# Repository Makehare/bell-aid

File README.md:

# bell-aid

Bell Aid

Release v1.3.1.

## Contents

- `docs/`
- `electronics/`
- `firmware/`
- `mechanics/`

## License

Hardware CERN-OHL-P-2.0, firmware MIT, documentation and renders CC-BY-4.0 (see LICENSE).

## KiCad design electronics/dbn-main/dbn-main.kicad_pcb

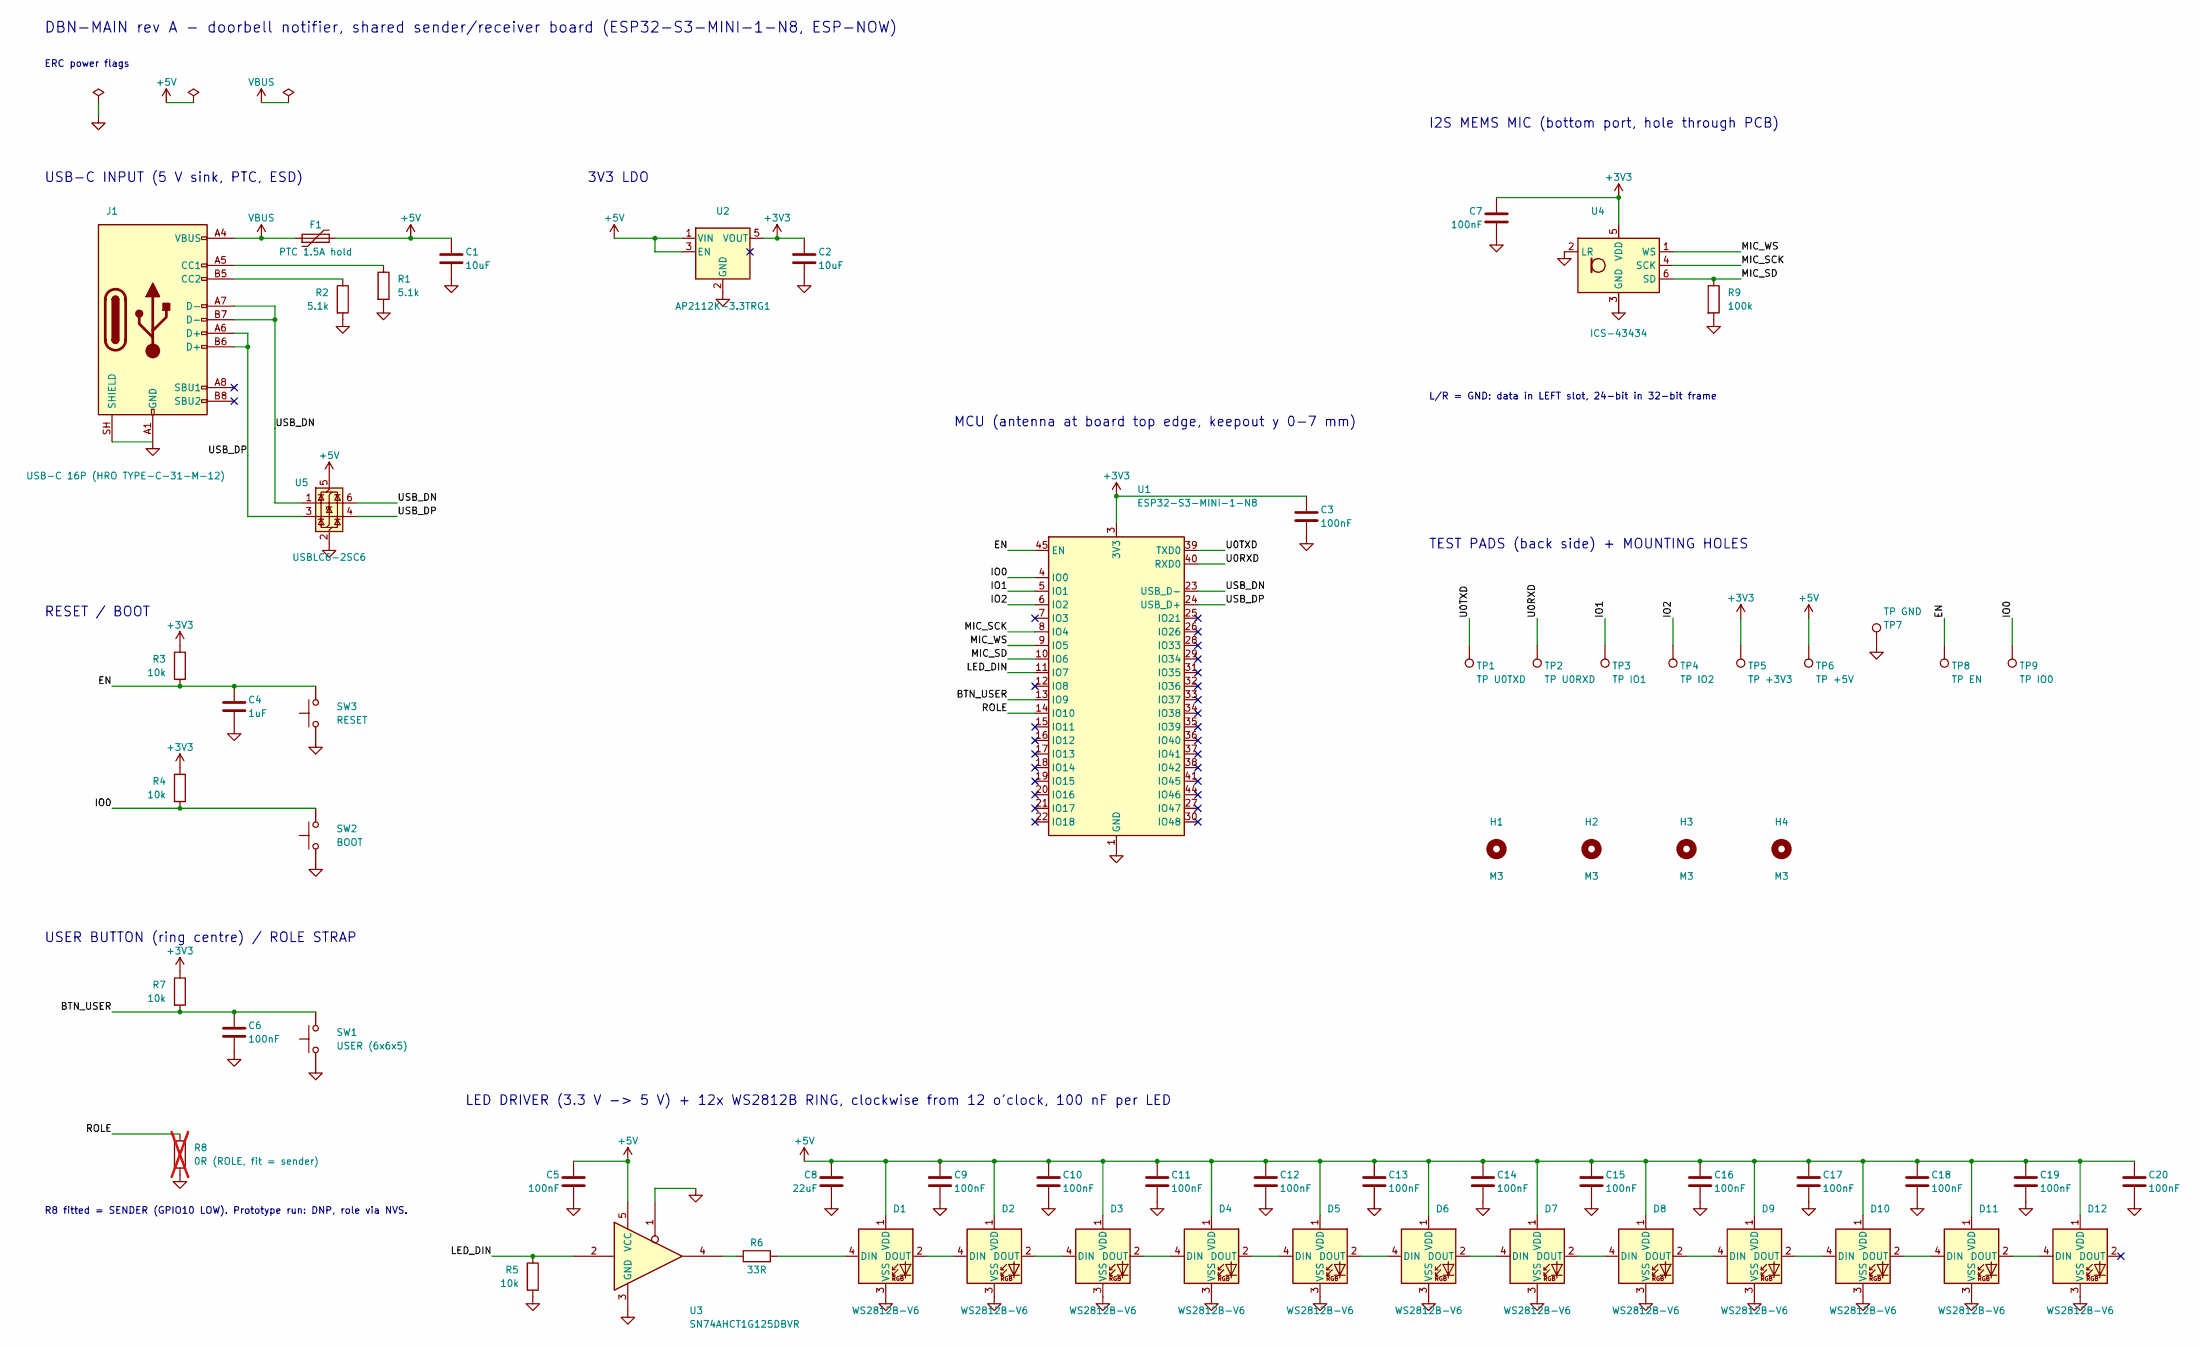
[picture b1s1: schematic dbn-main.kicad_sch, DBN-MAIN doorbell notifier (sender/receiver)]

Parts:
C1, C2: 10uF; C_0805_2012Metric; MPN CL21A106KAYNNNE; LCSC C15850
C3, C5, C6, C7, C9, C10, C11, C12, C13, C14, C15, C16, C17, C18, C19, C20: 100nF; C_0603_1608Metric; MPN CC0603KRX7R9BB104; LCSC C14663
C4: 1uF; C_0603_1608Metric; MPN CL10A105KB8NNNC; LCSC C15849
C8: 22uF; C_0805_2012Metric; MPN CL21A226MAQNNNE; LCSC C45783
D1, D2, D3, D4, D5, D6, D7, D8, D9, D10, D11, D12: WS2812B-V6; LED_WS2812B_PLCC4_5.0x5.0mm_P3.2mm; MPN WS2812B-V6; LCSC C52917433
F1: PTC 1.5A hold; Fuse_1206_3216Metric; MPN 1206L150THWR; LCSC C118413
H1, H2, H3, H4: M3; MountingHole_3.2mm_M3_NPTH
J1: USB-C 16P (HRO TYPE-C-31-M-12); USB_C_Receptacle_HRO_TYPE-C-31-M-12; MPN TYPE-C-31-M-12; LCSC C165948
R1, R2: 5.1k; R_0603_1608Metric; MPN 0603WAF5101T5E; LCSC C23186
R3, R4, R5, R7: 10k; R_0603_1608Metric; MPN 0603WAF1002T5E; LCSC C25804
R6: 33R; R_0603_1608Metric; MPN 0603WAF330JT5E; LCSC C23140
R8: 0R (ROLE, fit = sender); R_0603_1608Metric; MPN 0603WAF0000T5E; LCSC C21189; not fitted
R9: 100k; R_0603_1608Metric; MPN 0603WAF1003T5E; LCSC C25803
SW1: USER (6x6x5); SW_K2-1102SP-C4SC-04_6x6x5mm; MPN K2-1102SP-C4SC-04; LCSC C127509
SW2: BOOT; SW_Push_1P1T_XKB_TS-1187A; MPN TS-1187A-B-A-B; LCSC C318884
SW3: RESET; SW_Push_1P1T_XKB_TS-1187A; MPN TS-1187A-B-A-B; LCSC C318884
TP1: TP U0TXD; TestPoint_Pad_D1.5mm
TP2: TP U0RXD; TestPoint_Pad_D1.5mm
TP3: TP IO1; TestPoint_Pad_D1.5mm
TP4: TP IO2; TestPoint_Pad_D1.5mm
TP5: TP +3V3; TestPoint_Pad_D1.5mm
TP6: TP +5V; TestPoint_Pad_D1.5mm
TP7: TP GND; TestPoint_Pad_D1.5mm
TP8: TP EN; TestPoint_Pad_D1.5mm
TP9: TP IO0; TestPoint_Pad_D1.5mm
U1: ESP32-S3-MINI-1-N8; ESP32-S3-MINI-1; MPN ESP32-S3-MINI-1-N8; LCSC C2913206
U2: AP2112K-3.3TRG1; SOT-23-5; MPN AP2112K-3.3TRG1; LCSC C51118
U3: SN74AHCT1G125DBVR; SOT-23-5; MPN SN74AHCT1G125DBVR; LCSC C7484
U4: ICS-43434; InvenSense_ICS-43434-6_3.5x2.65mm; MPN ICS-43434; LCSC C5656610
U5: USBLC6-2SC6; SOT-23-6; MPN USBLC6-2SC6; LCSC C7519

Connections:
+3V3: C2.1, C3.1, C7.1, R3.1, R4.1, R7.1, TP5.1, U1.3 (3V3), U2.5 (VOUT), U4.5 (VDD)
+5V: C1.1, C5.1, C8.1, C9.1, C10.1, C11.1, C12.1, C13.1, C14.1, C15.1, C16.1, C17.1, C18.1, C19.1, C20.1, D1.1 (VDD), D2.1 (VDD), D3.1 (VDD), D4.1 (VDD), D5.1 (VDD), D6.1 (VDD), D7.1 (VDD), D8.1 (VDD), D9.1 (VDD), D10.1 (VDD), D11.1 (VDD), D12.1 (VDD), F1.2, TP6.1, U2.1 (VIN), U2.3 (EN), U3.5 (VCC), U5.5 (VBUS)
/BTN_USER: C6.1, R7.2, SW1.2, U1.13 (IO9)
/EN: C4.1, R3.2, SW3.2, TP8.1, U1.45 (EN)
/IO0: R4.2, SW2.2, TP9.1, U1.4 (IO0)
/IO1: TP3.1, U1.5 (IO1)
/IO2: TP4.1, U1.6 (IO2)
/LED_DIN: R5.1, U1.11 (IO7), U3.2
/MIC_SCK: U1.8 (IO4), U4.4 (SCK)
/MIC_SD: R9.1, U1.10 (IO6), U4.6 (SD)
/MIC_WS: U1.9 (IO5), U4.1 (WS)
/ROLE: R8.1, U1.14 (IO10)
/U0RXD: TP2.1, U1.40 (RXD0)
/U0TXD: TP1.1, U1.39 (TXD0)
/USB_DN: J1.A7 (D-), J1.B7 (D-), U1.23 (USB_D-), U5.1 (I/O1), U5.6 (I/O1)
/USB_DP: J1.A6 (D+), J1.B6 (D+), U1.24 (USB_D+), U5.3 (I/O2), U5.4 (I/O2)
GND: C1.2, C2.2, C3.2, C4.2, C5.2, C6.2, C7.2, C8.2, C9.2, C10.2, C11.2, C12.2, C13.2, C14.2, C15.2, C16.2, C17.2, C18.2, C19.2, C20.2, D1.3 (VSS), D2.3 (VSS), D3.3 (VSS), D4.3 (VSS), D5.3 (VSS), D6.3 (VSS), D7.3 (VSS), D8.3 (VSS), D9.3 (VSS), D10.3 (VSS), D11.3 (VSS), D12.3 (VSS), J1.A1 (GND), J1.A12 (GND), J1.B1 (GND), J1.B12 (GND), J1.SH (SHIELD), R1.2, R2.2, R5.2, R8.2, R9.2, SW1.1, SW2.1, SW3.1, TP7.1, U1.1 (GND), U1.2 (GND), U1.42 (GND), U1.43 (GND), U1.46 (GND), U1.47 (GND), U1.48 (GND), U1.49 (GND), U1.50 (GND), U1.51 (GND), U1.52 (GND), U1.53 (GND), U1.54 (GND), U1.55 (GND), U1.56 (GND), U1.57 (GND), U1.58 (GND), U1.59 (GND), U1.60 (GND), U1.61 (GND), U1.62 (GND), U1.63 (GND), U1.64 (GND), U1.65 (GND), U2.2 (GND), U3.1, U3.3 (GND), U4.2 (LR), U4.3 (GND), U5.2 (GND)
unnamed: D1.4 (DIN), R6.2
unnamed: D1.2 (DOUT), D2.4 (DIN)
unnamed: D2.2 (DOUT), D3.4 (DIN)
unnamed: D3.2 (DOUT), D4.4 (DIN)
unnamed: D4.2 (DOUT), D5.4 (DIN)
unnamed: D5.2 (DOUT), D6.4 (DIN)
unnamed: D6.2 (DOUT), D7.4 (DIN)
unnamed: D7.2 (DOUT), D8.4 (DIN)
unnamed: D8.2 (DOUT), D9.4 (DIN)
unnamed: D9.2 (DOUT), D10.4 (DIN)
unnamed: D10.2 (DOUT), D11.4 (DIN)
unnamed: D11.2 (DOUT), D12.4 (DIN)
unnamed: J1.A5 (CC1), R1.1
unnamed: J1.B5 (CC2), R2.1
unnamed: R6.1, U3.4
VBUS: F1.1, J1.A4 (VBUS), J1.A9 (VBUS), J1.B4 (VBUS), J1.B9 (VBUS)

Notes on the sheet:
DBN-MAIN rev A - doorbell notifier, shared sender/receiver board (ESP32-S3-MINI-1-N8, ESP-NOW)
ERC power flags
USB-C INPUT (5 V sink, PTC, ESD)
3V3 LDO
MCU (antenna at board top edge, keepout y 0-7 mm)
RESET / BOOT
USER BUTTON (ring centre) / ROLE STRAP
R8 fitted = SENDER (GPIO10 LOW). Prototype run: DNP, role via NVS.
I2S MEMS MIC (bottom port, hole through PCB)
L/R = GND: data in LEFT slot, 24-bit in 32-bit frame
LED DRIVER (3.3 V -> 5 V) + 12x WS2812B RING, clockwise from 12 o'clock, 100 nF per LED
TEST PADS (back side) + MOUNTING HOLES

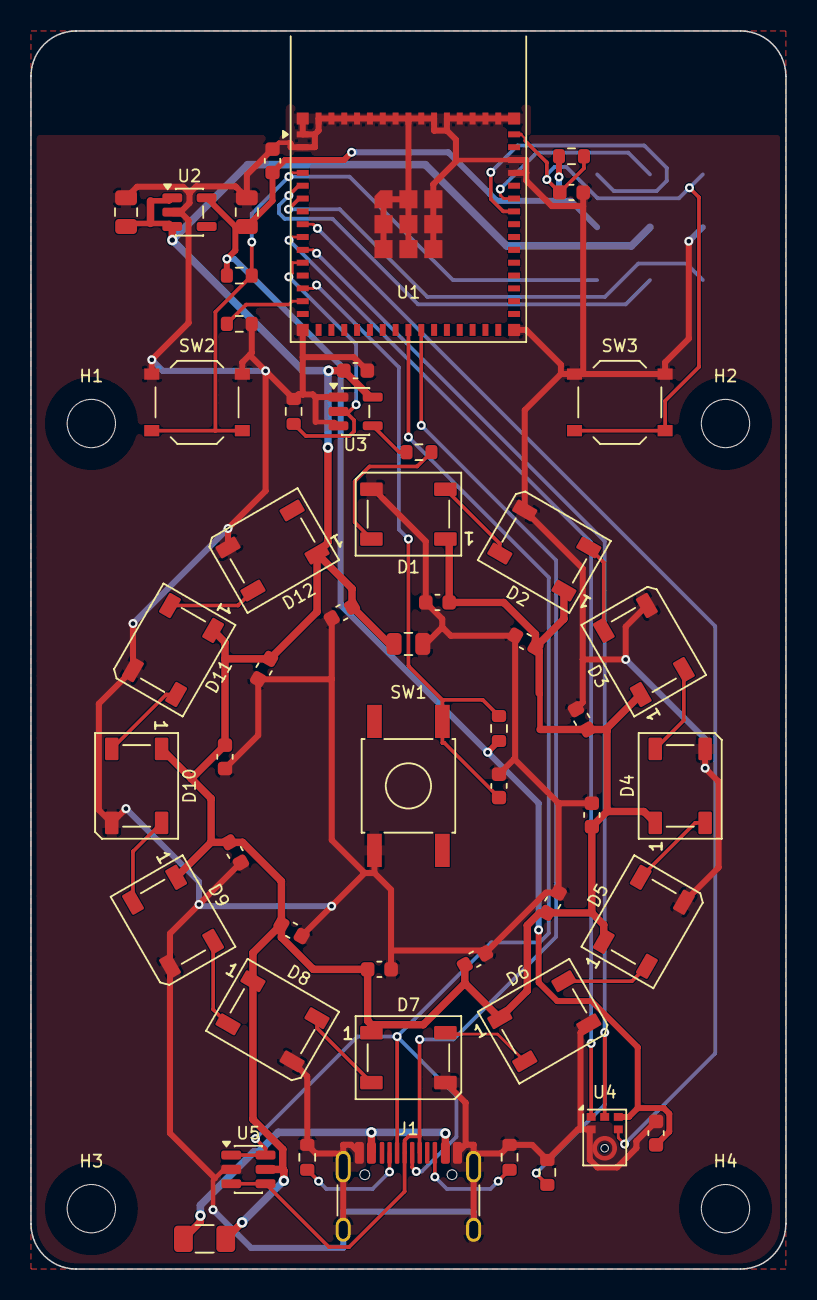
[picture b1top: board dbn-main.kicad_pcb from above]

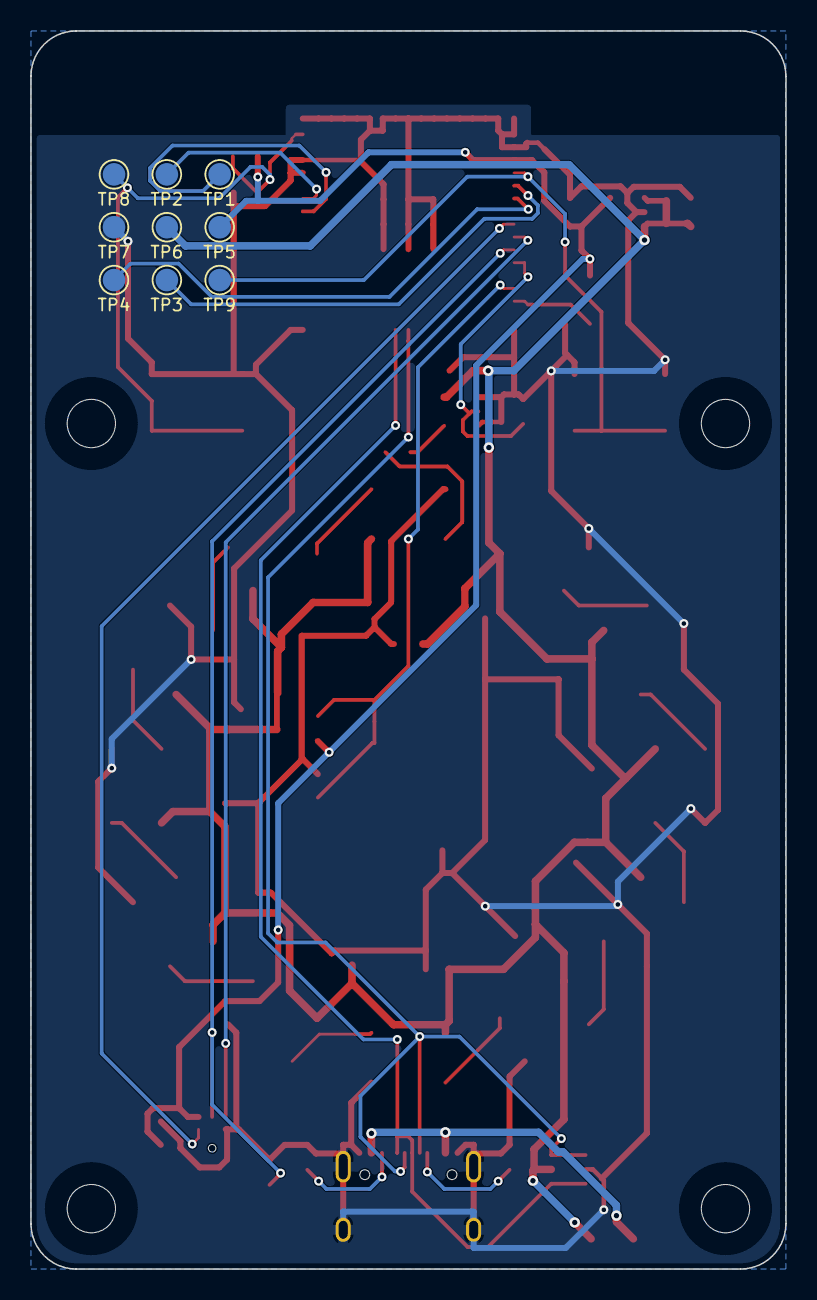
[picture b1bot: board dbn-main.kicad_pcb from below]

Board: 2 copper layers, 50.0 x 82.0 mm, 64 parts (9 on the bottom side), 33 nets.

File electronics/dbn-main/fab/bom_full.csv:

"Refs","Value","Footprint","LCSC","MPN","Qty","DNP"
"C1,C2","10uF","Capacitor_SMD:C_0805_2012Metric","C15850","CL21A106KAYNNNE","2",""
"C3,C5,C6,C7,C9,C10,C11,C12,C13,C14,C15,C16,C17,C18,C19,C20","100nF","Capacitor_SMD:C_0603_1608Metric","C14663","CC0603KRX7R9BB104","16",""
"C4","1uF","Capacitor_SMD:C_0603_1608Metric","C15849","CL10A105KB8NNNC","1",""
"C8","22uF","Capacitor_SMD:C_0805_2012Metric","C45783","CL21A226MAQNNNE","1",""
"D1,D2,D3,D4,D5,D6,D7,D8,D9,D10,D11,D12","WS2812B-V6","LED_SMD:LED_WS2812B_PLCC4_5.0x5.0mm_P3.2mm","C52917433","WS2812B-V6","12",""
"F1","PTC 1.5A hold","Fuse:Fuse_1206_3216Metric","C118413","1206L150THWR","1",""
"J1","USB-C 16P (HRO TYPE-C-31-M-12)","dbn-main:USB_C_Receptacle_HRO_TYPE-C-31-M-12","C165948","TYPE-C-31-M-12","1",""
"R1,R2","5.1k","Resistor_SMD:R_0603_1608Metric","C23186","0603WAF5101T5E","2",""
"R3,R4,R5,R7","10k","Resistor_SMD:R_0603_1608Metric","C25804","0603WAF1002T5E","4",""
"R6","33R","Resistor_SMD:R_0603_1608Metric","C23140","0603WAF330JT5E","1",""
"R8","0R (ROLE, fit = sender)","Resistor_SMD:R_0603_1608Metric","C21189","0603WAF0000T5E","1","DNP"
"R9","100k","Resistor_SMD:R_0603_1608Metric","C25803","0603WAF1003T5E","1",""
"SW1","USER (6x6x5)","dbn-main:SW_K2-1102SP-C4SC-04_6x6x5mm","C127509","K2-1102SP-C4SC-04","1",""
"SW2","BOOT","dbn-main:SW_Push_1P1T_XKB_TS-1187A","C318884","TS-1187A-B-A-B","1",""
"SW3","RESET","dbn-main:SW_Push_1P1T_XKB_TS-1187A","C318884","TS-1187A-B-A-B","1",""
"U1","ESP32-S3-MINI-1-N8","dbn-main:ESP32-S3-MINI-1","C2913206","ESP32-S3-MINI-1-N8","1",""
"U2","AP2112K-3.3TRG1","Package_TO_SOT_SMD:SOT-23-5","C51118","AP2112K-3.3TRG1","1",""
"U3","SN74AHCT1G125DBVR","Package_TO_SOT_SMD:SOT-23-5","C7484","SN74AHCT1G125DBVR","1",""
"U4","ICS-43434","Sensor_Audio:InvenSense_ICS-43434-6_3.5x2.65mm","C5656610","ICS-43434","1",""
"U5","USBLC6-2SC6","Package_TO_SOT_SMD:SOT-23-6","C7519","USBLC6-2SC6","1",""

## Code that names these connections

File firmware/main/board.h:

#pragma once
// Pin map: ARCHITECTURE.md sec. 4.4 (ESP32-S3-MINI-1-N8)
#define PIN_MIC_SCK   4     /* I2S BCLK  (sender) */
#define PIN_MIC_WS    5     /* I2S LRCLK (sender) */
#define PIN_MIC_SD    6     /* ICS-43434 data in (L/R=GND -> left slot, 24-bit in 32-bit frame); 100k pull-down on net */
#define PIN_LED_DIN   7     /* via 74AHCT1G125 to WS2812B chain, GRB */
#define PIN_BTN_USER  9     /* active LOW, external pull-up */
#define PIN_ROLE      10    /* internal pull-up; LOW = sender (R8 ROLE 0R to GND), HIGH = receiver. Prototype: R8 DNP -> all boards HIGH -> senders need NVS override */

#define NUM_LEDS      12    /* chain length on a receiver; sender uses pixel 0 only */
#define LED_CAP_MA    600   /* ring current cap, see dbn_common */

#define ESPNOW_CHANNEL 1
